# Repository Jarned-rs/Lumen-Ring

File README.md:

# Lumen-Ring

The lumen ring is a simple project designed to teach myself about charlieplexing and how it works in real situations. It reacts on the volume that your PC is set to and has a OLED to show upcoming events for you that can be changed easily in the code.

# Features
- RP2040-Zero to control the LEDS and OLED
- OLED to display your upcoming events
- 20 LEDS charlieplexed in 5pin with 3 colours to correspond with your PC's volume
- A rotary encoder to turn your volume up, down and mute sound
- A case with a hinge to keep the LEDs and OLED safe during storage! 

# How it works
On a basic GPIO port, we have 2 main modes that they can be in, either HIGH or LOW. Charlieplexing uses a 3rd mode called INPUT to fit more LEDS on one pin.
- A script reads the volume and sends it via USB to the 2040
- The 2040 reads the volume and decides how many LEDS need to be switched on
- It finds the right LEDs and turns them on

# Photos
Case:

Schematic:

PCB:

BOM:
|Part|QTY|Price|Link|Note|
|----------|---------|-----|-------------|--------|
|RP2040-Zero|1|0|N/A|Already Owned|
|LEDs|20|$1.35|https://www.aliexpress.com/item/1005004966964656.html?spm=a2g0o.detail.0.0.72c7Vs5tVs5tkD&mp=1||
|Resistors|5|$5.55|https://www.aliexpress.com/item/1005011772534173.html?spm=a2g0o.cart.0.0.778838daPJe0Vl&mp=1||
|0.96" OLED|1|$2.23|https://www.aliexpress.com/item/1005006827999782.html?spm=a2g0o.cart.0.0.6f1e38daj4PjJx&mp=1||
|Case|1|$5|N/A|Friend is printing for me|

Total = $14.14

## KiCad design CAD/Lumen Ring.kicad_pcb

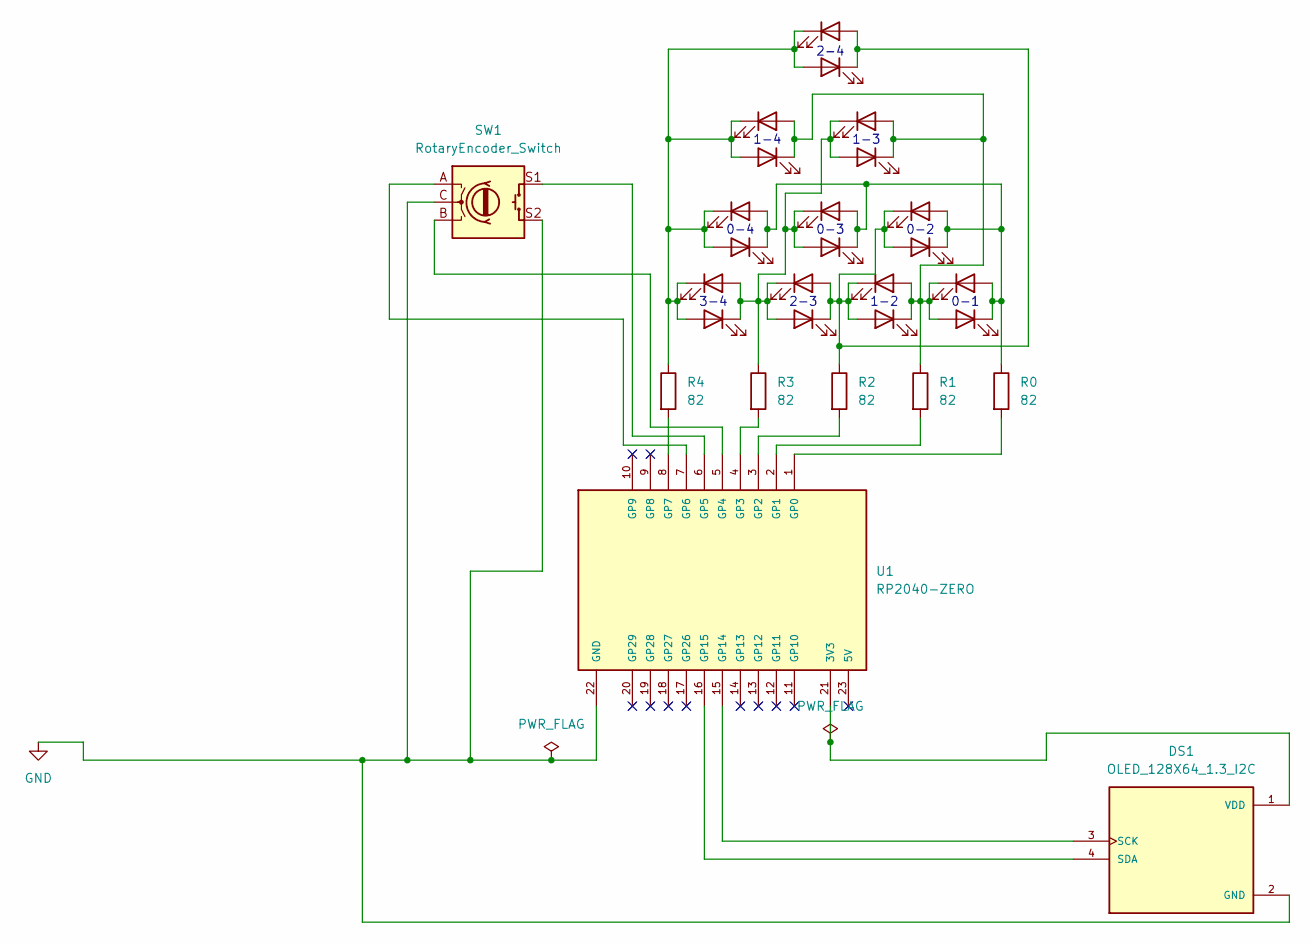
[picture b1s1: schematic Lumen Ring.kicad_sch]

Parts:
D1, D2, D3, D4, D5, D6, D9, D10, D11, D12, D13, D14, D15, D16, D17, D18, D19, D20, D21, D22: LED; LED_D5.0mm
DS1: OLED_128X64_1.3_I2C; LCD_OLED_128X64_1.3_I2C; PARTREV NA
R0, R1, R2, R3, R4: 82; R_Axial_DIN0207_L6.3mm_D2.5mm_P7.62mm_Horizontal
SW1: RotaryEncoder_Switch; RotaryEncoder_Alps_EC11E-Switch_Vertical_H20mm
U1: RP2040-ZERO; MODULE_RP2040-ZERO; PARTREV NA

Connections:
GND: DS1.2 (GND), SW1.C, SW1.S2, U1.22 (GND)
unnamed: D1.2 (A), D2.1 (K), D11.2 (A), D12.1 (K), D13.2 (A), D14.1 (K), D15.2 (A), D16.1 (K), R0.1
unnamed: D1.1 (K), D2.2 (A), D3.2 (A), D4.1 (K), D17.2 (A), D18.1 (K), D19.2 (A), D20.1 (K), R1.1
unnamed: D9.1 (K), D10.2 (A), D15.1 (K), D16.2 (A), D19.1 (K), D20.2 (A), D21.1 (K), D22.2 (A), R4.1
unnamed: D5.1 (K), D6.2 (A), D9.2 (A), D10.1 (K), D13.1 (K), D14.2 (A), D17.1 (K), D18.2 (A), R3.1
unnamed: D3.1 (K), D4.2 (A), D5.2 (A), D6.1 (K), D11.1 (K), D12.2 (A), D21.2 (A), D22.1 (K), R2.1
unnamed: DS1.3 (SCK), U1.15 (GP14)
unnamed: DS1.4 (SDA), U1.16 (GP15)
unnamed: DS1.1 (VDD), U1.21 (3V3)
unnamed: R0.2, U1.1 (GP0)
unnamed: R1.2, U1.2 (GP1)
unnamed: R2.2, U1.3 (GP2)
unnamed: R3.2, U1.4 (GP3)
unnamed: SW1.B, U1.5 (GP4)
unnamed: SW1.S1, U1.6 (GP5)
unnamed: SW1.A, U1.7 (GP6)
unnamed: R4.2, U1.8 (GP7)

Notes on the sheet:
0-2
3-4
2-3
1-3
0-3
0-1
0-4
1-2
2-4
1-4

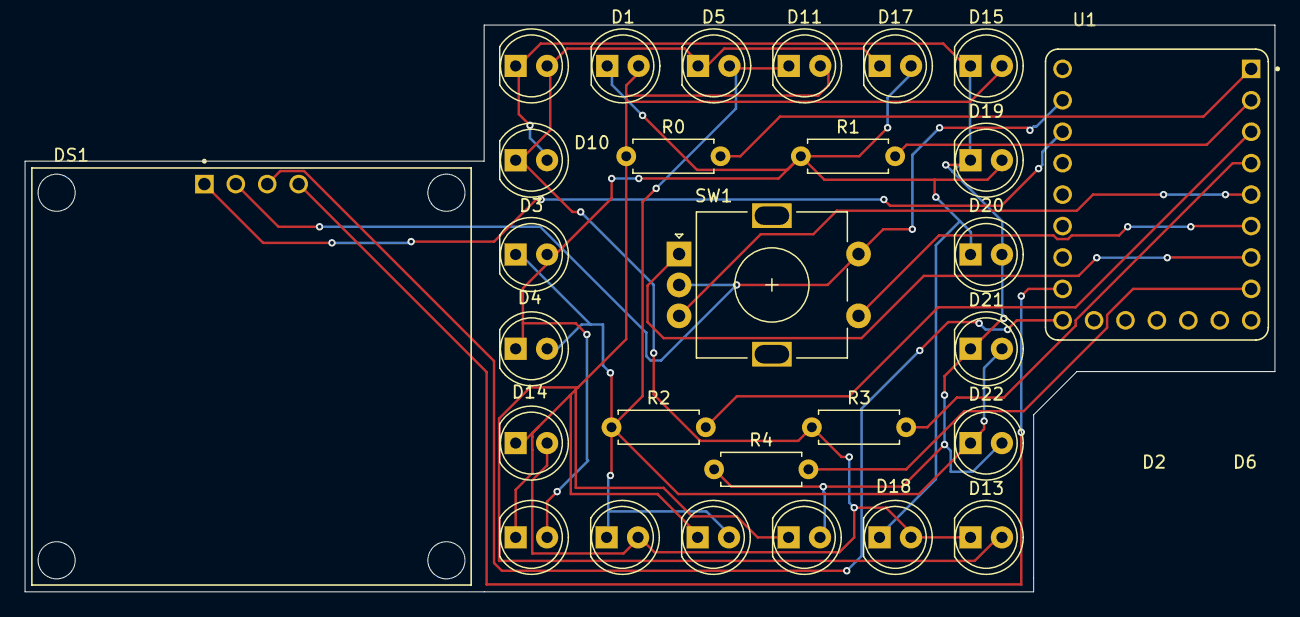
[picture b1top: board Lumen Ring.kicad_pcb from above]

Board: 2 copper layers, 101.0 x 45.8 mm, 28 parts (0 on the bottom side), 17 nets.
